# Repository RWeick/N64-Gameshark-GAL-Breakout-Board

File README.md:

# N64-Gameshark-GAL-Breakout-Board
The kicad files for my custom N64 Gameshark breakout board to facilitate logic analysis of the GAL. The pin headers are 2.54 mm.

PCB Thickness: 1.2 mm

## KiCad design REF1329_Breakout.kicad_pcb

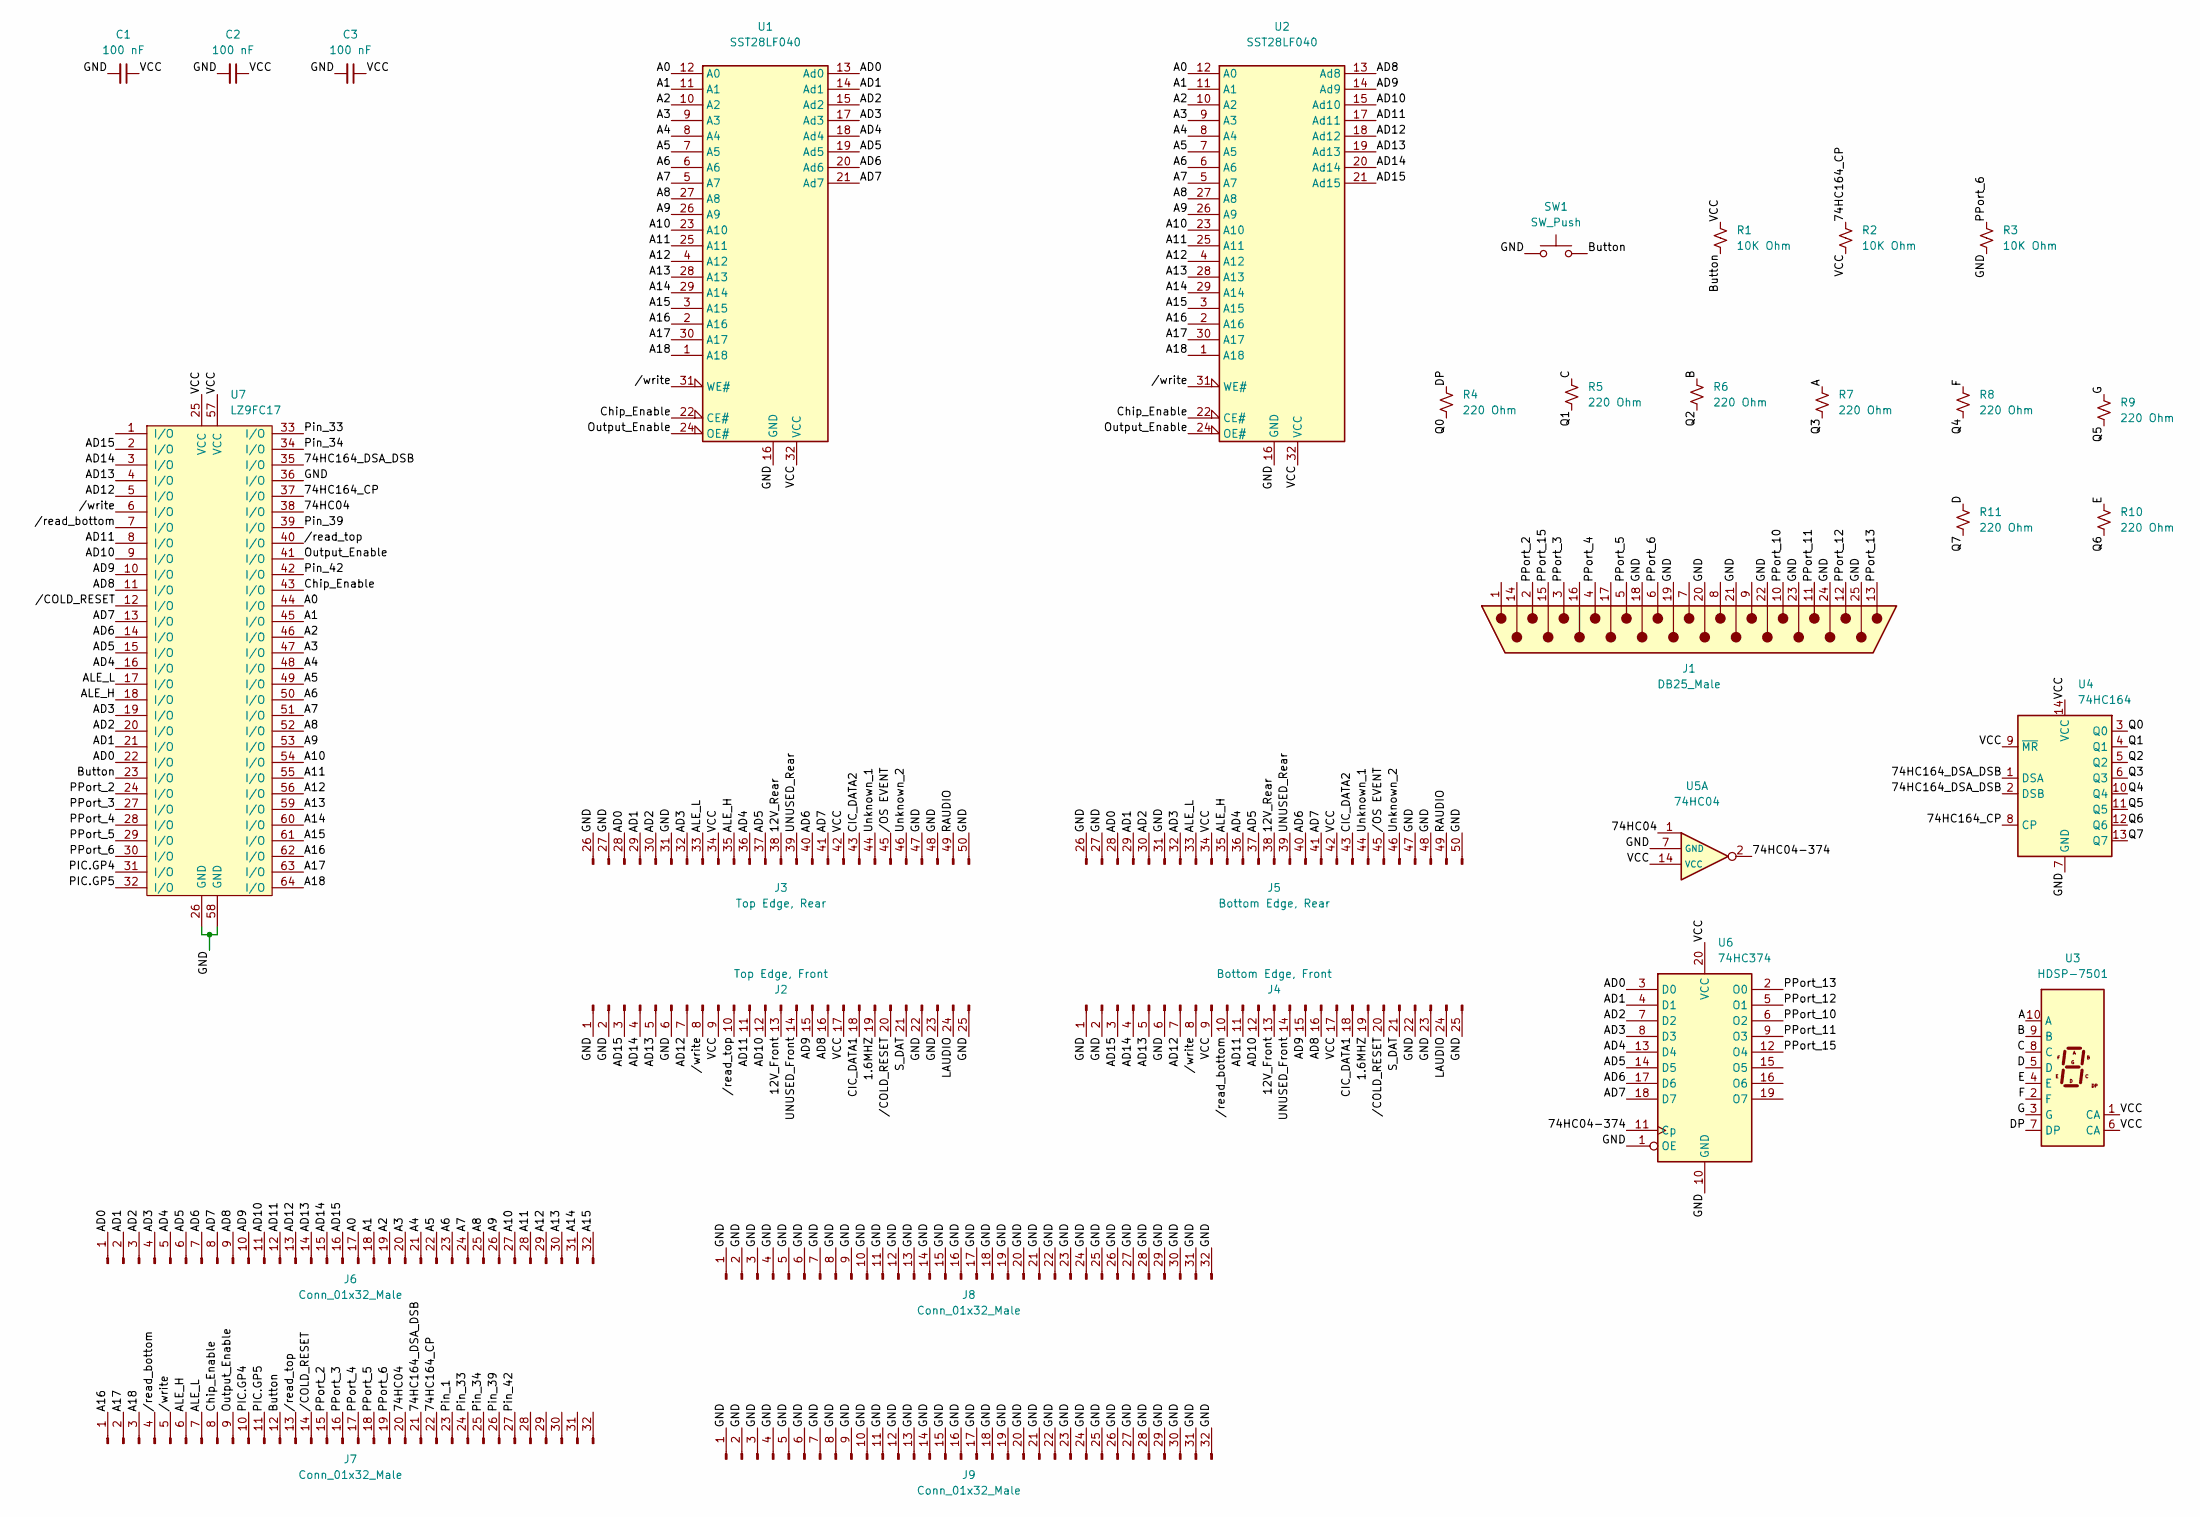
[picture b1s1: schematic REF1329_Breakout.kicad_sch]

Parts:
C1, C2, C3: 100 nF; 100 nF Cap
J1: DB25_Male; DSUB-25_Male_Vertical_P2.77x2.84mm
J2: Top Edge, Front; Cart Edge Connector
J3: Top Edge, Rear; Cart Edge Connector Back
J4: Bottom Edge, Front; Cart Edge Connector
J5: Bottom Edge, Rear; Cart Edge Connector Back
J6, J7, J8, J9: Conn_01x32_Male; PinHeader_1x32_P2.54mm_Vertical
R1, R2, R3: 10K Ohm; 10k Ohm Resistor
R4, R5, R6, R7, R8, R9, R10, R11: 220 Ohm; 220 Ohm Resistor
SW1: SW_Push; 1mm Push Button
U1, U2: SST28LF040; PLCC32
U3: HDSP-7501; HDSP-7401
U4: 74HC164
U5: 74HC04; 74HC04M
U6: 74HC374
U7: LZ9FC17; LZ9FC17 GAL

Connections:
/1.6MHZ: J2.19, J4.19
/12V_Front: J2.13, J4.13
/12V_Rear: J3.38 (Pin_13), J5.38 (Pin_13)
/74HC04: J7.20, U5.1, U7.38 (I/O)
/74HC04-374: U5.2, U6.11 (Cp)
/74HC164_CP: J7.22, R2.1, U4.8 (CP), U7.37 (I/O)
/74HC164_DSA_DSB: J7.21, U4.1 (DSA), U4.2 (DSB), U7.35 (I/O)
/A: R7.1, U3.10 (A)
/A0: J6.17, U1.12 (A0), U2.12 (A0), U7.44 (I/O)
/A1: J6.18, U1.11 (A1), U2.11 (A1), U7.45 (I/O)
/A2: J6.19, U1.10 (A2), U2.10 (A2), U7.46 (I/O)
/A3: J6.20, U1.9 (A3), U2.9 (A3), U7.47 (I/O)
/A4: J6.21, U1.8 (A4), U2.8 (A4), U7.48 (I/O)
/A5: J6.22, U1.7 (A5), U2.7 (A5), U7.49 (I/O)
/A6: J6.23, U1.6 (A6), U2.6 (A6), U7.50 (I/O)
/A7: J6.24, U1.5 (A7), U2.5 (A7), U7.51 (I/O)
/A8: J6.25, U1.27 (A8), U2.27 (A8), U7.52 (I/O)
/A9: J6.26, U1.26 (A9), U2.26 (A9), U7.53 (I/O)
/A10: J6.27, U1.23 (A10), U2.23 (A10), U7.54 (I/O)
/A11: J6.28, U1.25 (A11), U2.25 (A11), U7.55 (I/O)
/A12: J6.29, U1.4 (A12), U2.4 (A12), U7.56 (I/O)
/A13: J6.30, U1.28 (A13), U2.28 (A13), U7.59 (I/O)
/A14: J6.31, U1.29 (A14), U2.29 (A14), U7.60 (I/O)
/A15: J6.32, U1.3 (A15), U2.3 (A15), U7.61 (I/O)
/A16: J7.1, U1.2 (A16), U2.2 (A16), U7.62 (I/O)
/A17: J7.2, U1.30 (A17), U2.30 (A17), U7.63 (I/O)
/A18: J7.3, U1.1 (A18), U2.1 (A18), U7.64 (I/O)
/AD0: J3.28 (Pin_3), J5.28 (Pin_23), J6.1, U1.13 (Ad0), U6.3 (D0), U7.22 (I/O)
/AD1: J3.29 (Pin_4), J5.29 (Pin_22), J6.2, U1.14 (Ad1), U6.4 (D1), U7.21 (I/O)
/AD2: J3.30 (Pin_5), J5.30 (Pin_21), J6.3, U1.15 (Ad2), U6.7 (D2), U7.20 (I/O)
/AD3: J3.32 (Pin_7), J5.32 (Pin_19), J6.4, U1.17 (Ad3), U6.8 (D3), U7.19 (I/O)
/AD4: J3.36 (Pin_11), J5.36 (Pin_15), J6.5, U1.18 (Ad4), U6.13 (D4), U7.16 (I/O)
/AD5: J3.37 (Pin_12), J5.37 (Pin_14), J6.6, U1.19 (Ad5), U6.14 (D5), U7.15 (I/O)
/AD6: J3.40 (Pin_15), J5.40 (Pin_11), J6.7, U1.20 (Ad6), U6.17 (D6), U7.14 (I/O)
/AD7: J3.41 (Pin_16), J5.41 (Pin_10), J6.8, U1.21 (Ad7), U6.18 (D7), U7.13 (I/O)
/AD8: J2.16, J4.16, J6.9, U2.13 (Ad8), U7.11 (I/O)
/AD9: J2.15, J4.15, J6.10, U2.14 (Ad9), U7.10 (I/O)
/AD10: J2.12, J4.12, J6.11, U2.15 (Ad10), U7.9 (I/O)
/AD11: J2.11, J4.11, J6.12, U2.17 (Ad11), U7.8 (I/O)
/AD12: J2.7, J4.7, J6.13, U2.18 (Ad12), U7.5 (I/O)
/AD13: J2.5, J4.5, J6.14, U2.19 (Ad13), U7.4 (I/O)
/AD14: J2.4, J4.4, J6.15, U2.20 (Ad14), U7.3 (I/O)
/AD15: J2.3, J4.3, J6.16, U2.21 (Ad15), U7.2 (I/O)
/ALE_H: J3.35 (Pin_10), J5.35 (Pin_16), J7.6, U7.18 (I/O)
/ALE_L: J3.33 (Pin_8), J5.33 (Pin_18), J7.7, U7.17 (I/O)
/B: R6.1, U3.9 (B)
/Button: J7.12, R1.1, SW1.2, U7.23 (I/O)
/C: R5.1, U3.8 (C)
/CIC_DATA1: J2.18, J4.18
/CIC_DATA2: J3.43 (Pin_18), J5.43 (Pin_8)
/Chip_Enable: J7.8, U1.22 (CE#), U2.22 (CE#), U7.43 (I/O)
/D: R11.1, U3.5 (D)
/DP: R4.1, U3.7 (DP)
/E: R10.1, U3.4 (E)
/F: R8.1, U3.2 (F)
/G: R9.1, U3.3 (G)
/GND: C1.2, C2.2, C3.2, J1.18, J1.19, J1.20, J1.21, J1.22, J1.23, J1.24, J1.25, J2.1, J2.2, J2.6, J2.22, J2.23, J2.25, J3.26 (Pin_1), J3.27 (Pin_2), J3.31 (Pin_6), J3.47 (Pin_22), J3.48 (Pin_23), J3.50 (Pin_25), J4.1, J4.2, J4.6, J4.22, J4.23, J4.25, J5.26 (Pin_25), J5.27 (Pin_24), J5.31 (Pin_20), J5.47 (Pin_4), J5.48 (Pin_3), J5.50 (Pin_1), J8.1, J8.2, J8.3, J8.4, J8.5, J8.6, J8.7, J8.8, J8.9, J8.10, J8.11, J8.12, J8.13, J8.14, J8.15, J8.16, J8.17, J8.18, J8.19, J8.20, J8.21, J8.22, J8.23, J8.24, J8.25, J8.26, J8.27, J8.28, J8.29, J8.30, J8.31, J8.32, J9.1, J9.2, J9.3, J9.4, J9.5, J9.6, J9.7, J9.8, J9.9, J9.10, J9.11, J9.12, J9.13, J9.14, J9.15, J9.16, J9.17, J9.18, J9.19, J9.20, J9.21, J9.22, J9.23, J9.24, J9.25, J9.26, J9.27, J9.28, J9.29, J9.30, J9.31, J9.32, R3.2, SW1.1, U1.16 (GND), U2.16 (GND), U4.7 (GND), U5.7 (GND), U6.1 (OE), U6.10 (GND), U7.26 (GND), U7.36 (I/O), U7.58 (GND)
/LAUDIO: J2.24, J4.24
/Output_Enable: J7.9, U1.24 (OE#), U2.24 (OE#), U7.41 (I/O)
/PIC.GP4: J7.10, U7.31 (I/O)
/PIC.GP5: J7.11, U7.32 (I/O)
/PPort_2: J1.2, J7.15, U7.24 (I/O)
/PPort_3: J1.3, J7.16, U7.27 (I/O)
/PPort_4: J1.4, J7.17, U7.28 (I/O)
/PPort_5: J1.5, J7.18, U7.29 (I/O)
/PPort_6: J1.6, J7.19, R3.1, U7.30 (I/O)
/PPort_10: J1.10, U6.6 (O2)
/PPort_11: J1.11, U6.9 (O3)
/PPort_12: J1.12, U6.5 (O1)
/PPort_13: J1.13, U6.2 (O0)
/PPort_15: J1.15, U6.12 (O4)
/Pin_1: J7.23
/Pin_33: J7.24, U7.33 (I/O)
/Pin_34: J7.25, U7.34 (I/O)
/Pin_39: J7.26, U7.39 (I/O)
/Pin_42: J7.27, U7.42 (I/O)
/Q0: R4.2, U4.3 (Q0)
/Q1: R5.2, U4.4 (Q1)
/Q2: R6.2, U4.5 (Q2)
/Q3: R7.2, U4.6 (Q3)
/Q4: R8.2, U4.10 (Q4)
/Q5: R9.2, U4.11 (Q5)
/Q6: R10.2, U4.12 (Q6)
/Q7: R11.2, U4.13 (Q7)
/RAUDIO: J3.49 (Pin_24), J5.49 (Pin_2)
/S_DAT: J2.21, J4.21
/UNUSED_Front: J2.14, J4.14
/UNUSED_Rear: J3.39 (Pin_14), J5.39 (Pin_12)
/Unknown_1: J3.44 (Pin_19), J5.44 (Pin_7)
/Unknown_2: J3.46 (Pin_21), J5.46 (Pin_5)
/VCC: C1.1, C2.1, C3.1, J2.9, J2.17, J3.34 (Pin_9), J3.42 (Pin_17), J4.9, J4.17, J5.34 (Pin_17), J5.42 (Pin_9), R1.2, R2.2, U1.32 (VCC), U2.32 (VCC), U3.1 (CA), U3.6 (CA), U4.9 (~MR), U4.14 (VCC), U5.14 (VCC), U6.20 (VCC), U7.25 (VCC), U7.57 (VCC)
//COLD_RESET: J2.20, J4.20, J7.14, U7.12 (I/O)
//OS EVENT: J3.45 (Pin_20), J5.45 (Pin_6)
//read_bottom: J4.10, J7.4, U7.7 (I/O)
//read_top: J2.10, J7.13, U7.40 (I/O)
//write: J2.8, J4.8, J7.5, U1.31 (WE#), U2.31 (WE#), U7.6 (I/O)

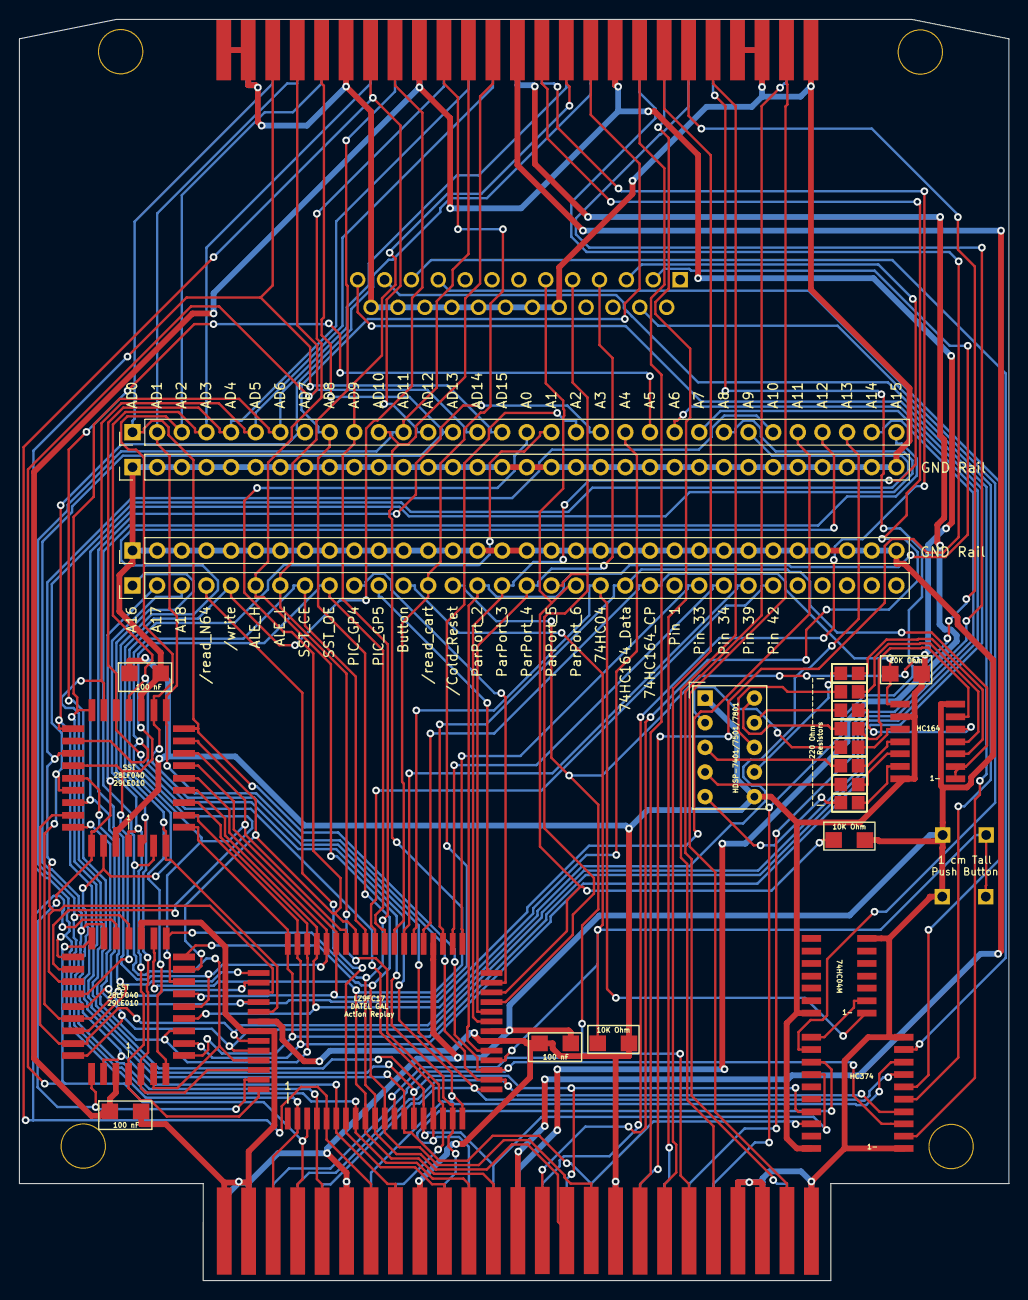
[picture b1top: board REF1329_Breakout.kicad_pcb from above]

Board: 2 copper layers, 102.0 x 130.0 mm, 35 parts (1 on the bottom side), 95 nets.

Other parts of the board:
Hole1, Hole2, Hole3, Hole4: N64-Hole
